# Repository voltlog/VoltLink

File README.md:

# VoltLink™
***If you would like to order one of these adapters ready assembled, check out my [Tindie store](https://www.tindie.com/products/23076/).***

VoltLink™ is a USB to serial adapter board based on the popular CP2102N chip with built-in ESP32 auto-reset circuitry. When compared to the cheap modules you can get from Aliexpress this adapter is reliable & flexible at the same time. Reliable because it's based on a well known usb to serial adapter chip sourced from a known supplier and flexible because you have the ESP32 IO & EN pin auto-reset circuit built-in so there is no need to implement this on the target board.

Another advantage of the VoltLink is the built-in 3.3V 500mA low dropout regulator capable of powering the device your are programming. Optionally you can connect a custom JST cable that alows programming of Shelly relays safely, without mains power. This makes the VoltLink one of the best usb/serial adapters to flash your devices with Tasmota or ESPHome.

You have the option of connecting through the VoltLink connector which is a JST-SH 1.0mm pitch 6 pin connector that saves space on the target board or via standard 0.1 inch pin header. 

More info about this project in [Voltlog #405](https://youtu.be/4uZt7zaJOnc).
> Please note, there have been several board revisions since I made that video.

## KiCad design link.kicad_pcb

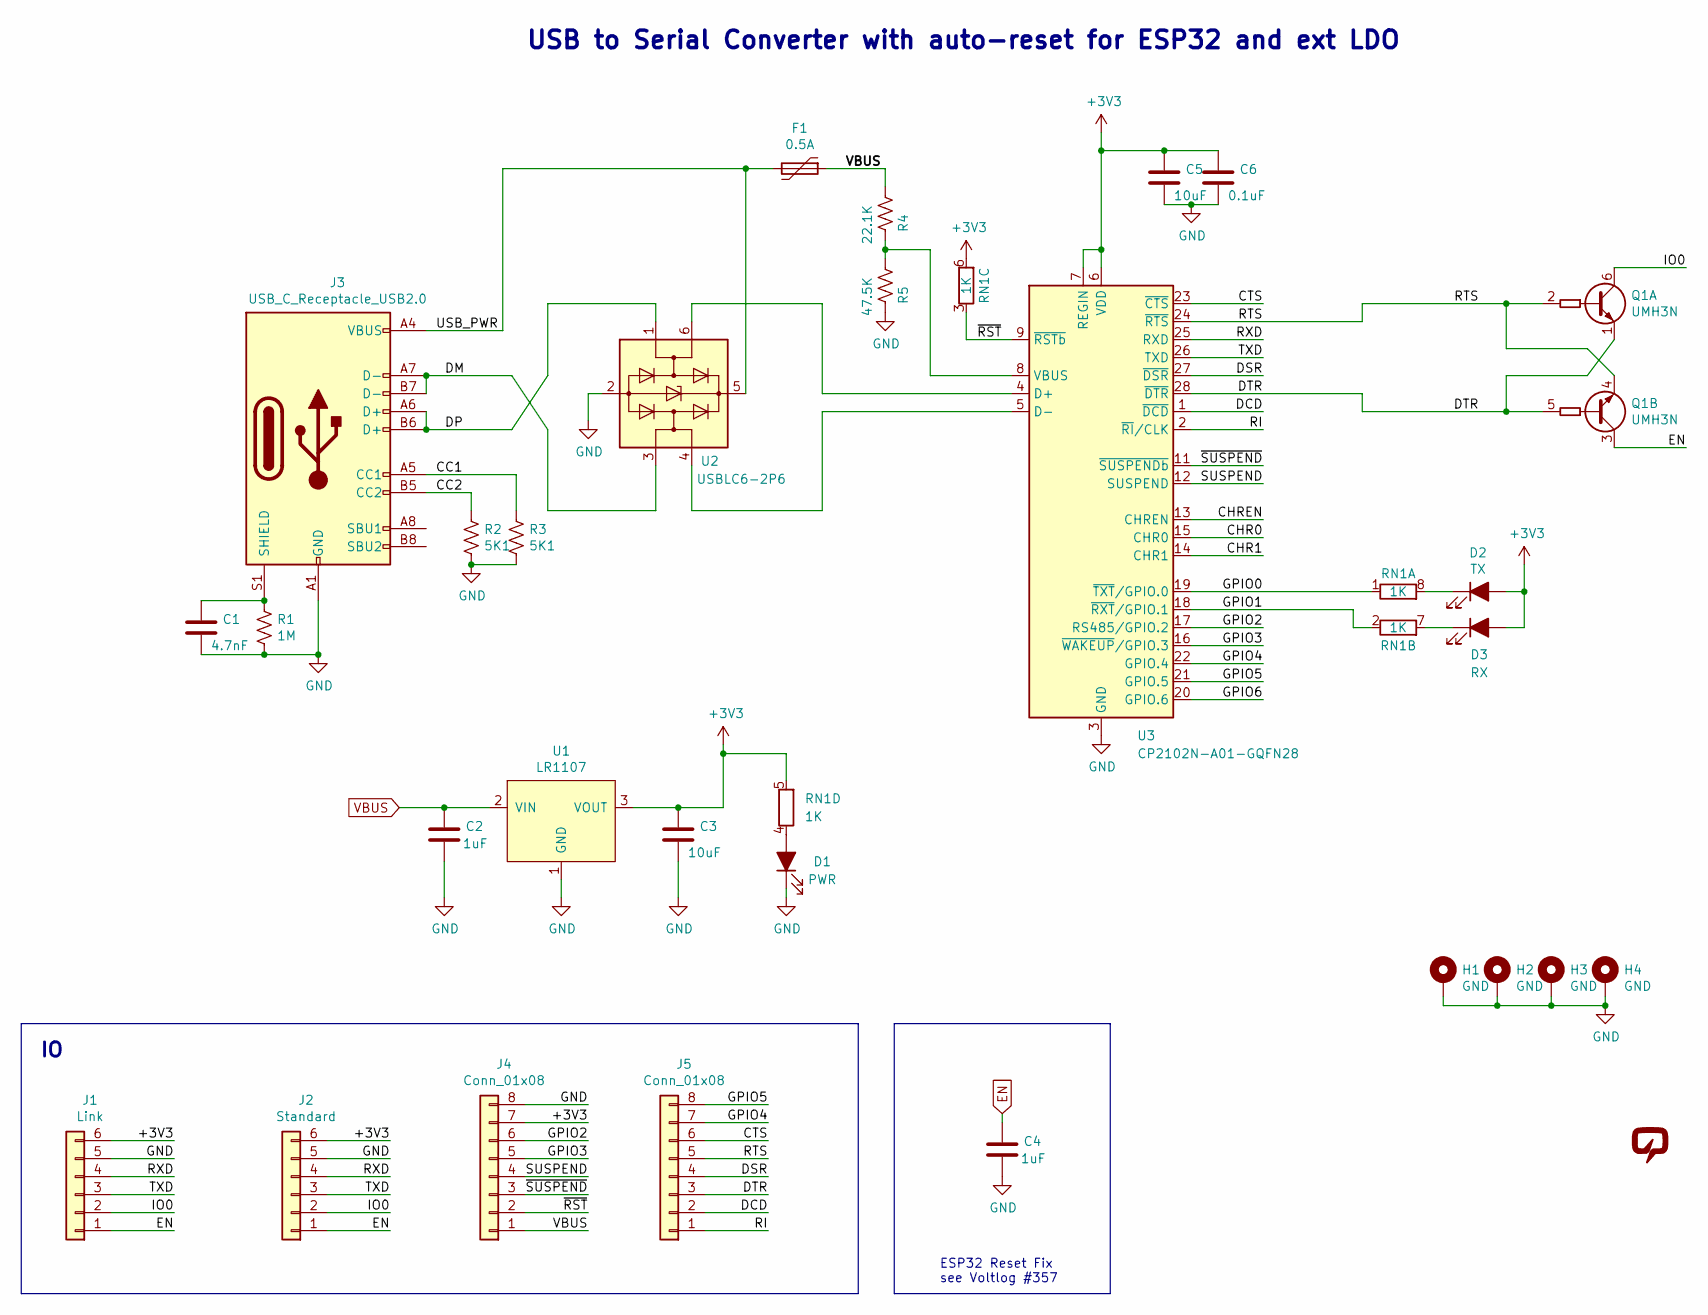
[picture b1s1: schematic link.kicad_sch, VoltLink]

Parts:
C1: 4.7nF; C_1206_3216Metric; Voltage 1KV; LCSC C107198
C2, C4: 1uF; C_0603_1608Metric; LCSC C15849
C3: 10uF; C_0603_1608Metric; Voltage 16V; LCSC C19702
C5: 10uF; C_0603_1608Metric; LCSC C19702
C6: 0.1uF; C_0603_1608Metric; LCSC C14663
D1: PWR; LED_0603_1608Metric; LCSC C193902
D2: TX; LED_0603_1608Metric; LCSC C84267
D3: RX; LED_0603_1608Metric; LCSC C193902
F1: 0.5A; Fuse_0603_1608Metric; LCSC C207014
H1, H2, H3, H4: GND; MountingHole_2.5mm_Pad
J1: Link; JST_SH_BM06B-SRSS-TB_1x06-1MP_P1.00mm_Vertical; LCSC C145963
J2: Standard; PinHeader_1x06_P2.54mm_Horizontal
J3: USB_C_Receptacle_USB2.0; TYPE-C-31-M-12; LCSC C165948
J4, J5: Conn_01x08; PinHeader_1x08_P2.54mm_Vertical
Q1: UMH3N; SOT-363_SC-70-6; LCSC C62892
R1: 1M; R_1206_3216Metric
R2, R3: 5K1; R_0603_1608Metric
R4: 22.1K; R_0603_1608Metric; LCSC C25961
R5: 47.5K; R_0603_1608Metric; LCSC C203634
RN1: 1K; R_Array_Convex_4x0603; LCSC C20197
U1: LR1107; SOT-89-3; LCSC C171498
U2: USBLC6-2P6; SOT-666; LCSC C2827693
U3: CP2102N-A01-GQFN28; QFN-28-1EP_5x5mm_P0.5mm_EP3.35x3.35mm; LCSC C1550553
V1: VOLTLOG_LOGO; voltlog_mask_3mm

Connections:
+3V3: C3.1, C5.1, C6.1, D2.2 (A), D3.2 (A), J1.6, J2.6, J4.7, RN1.5 (R4.2), RN1.6 (R3.2), U1.3 (VOUT), U3.6 (VDD), U3.7 (REGIN)
/CC1: J3.A5 (CC1), R3.1
/CC2: J3.B5 (CC2), R2.1
/CHR0: U3.15 (CHR0)
/CHR1: U3.14 (CHR1)
/CHREN: U3.13 (CHREN)
/CTS: J5.6, U3.23 (~CTS)
/DCD: J5.2, U3.1 (~DCD)
/DM: J3.A7 (D-), J3.B7 (D-), U2.3 (I/O2)
/DP: J3.A6 (D+), J3.B6 (D+), U2.1 (I/O1)
/DSR: J5.4, U3.27 (~DSR)
/DTR: J5.3, Q1.1 (E1), Q1.5 (B2), U3.28 (~DTR)
/GPIO0: RN1.1 (R1.1), U3.19 (~TXT/GPIO.0)
/GPIO1: RN1.2 (R2.1), U3.18 (~RXT/GPIO.1)
/GPIO2: J4.6, U3.17 (RS485/GPIO.2)
/GPIO3: J4.5, U3.16 (~WAKEUP/GPIO.3)
/GPIO4: J5.7, U3.22 (GPIO.4)
/GPIO5: J5.8, U3.21 (GPIO.5)
/GPIO6: U3.20 (GPIO.6)
/IO0: J1.2, J2.2, Q1.6 (C1)
/RI: J5.1, U3.2 (~RI/CLK)
/RTS: J5.5, Q1.2 (B1), Q1.4 (E2), U3.24 (~RTS)
/RXD: J1.4, J2.4, U3.25 (RXD)
/SUSPEND: J4.4, U3.12 (SUSPEND)
/TXD: J1.3, J2.3, U3.26 (TXD)
/USB_PWR: F1.2, J3.A4 (VBUS), J3.A9 (VBUS), J3.B4 (VBUS), J3.B9 (VBUS), U2.5 (VBUS)
/~RST: J4.2, RN1.3 (R3.1), U3.9 (~RSTb)
/~SUSPEND: J4.3, U3.11 (~SUSPENDb)
EN: C4.1, J1.1, J2.1, Q1.3 (C2)
GND: C1.2, C2.2, C3.2, C4.2, C5.2, C6.2, D1.1 (K), H1.1, H2.1, H3.1, H4.1, J1.5, J2.5, J3.A1 (GND), J3.A12 (GND), J3.B1 (GND), J3.B12 (GND), J4.8, R1.2, R2.2, R3.2, R5.2, U1.1 (GND), U2.2 (GND), U3.3 (GND), U3.29 (GND)
unnamed: C1.1, J3.S1 (SHIELD), R1.1
unnamed: D1.2 (A), RN1.4 (R4.1)
unnamed: D2.1 (K), RN1.8 (R1.2)
unnamed: D3.1 (K), RN1.7 (R2.2)
unnamed: R4.2, R5.1, U3.8 (VBUS)
unnamed: U2.4 (I/O2), U3.5 (D-)
unnamed: U2.6 (I/O1), U3.4 (D+)
VBUS: C2.1, F1.1, J4.1, R4.1, U1.2 (VIN)

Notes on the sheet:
ESP32 Reset Fix see Voltlog #357
USB to Serial Converter with auto-reset for ESP32 and ext LDO

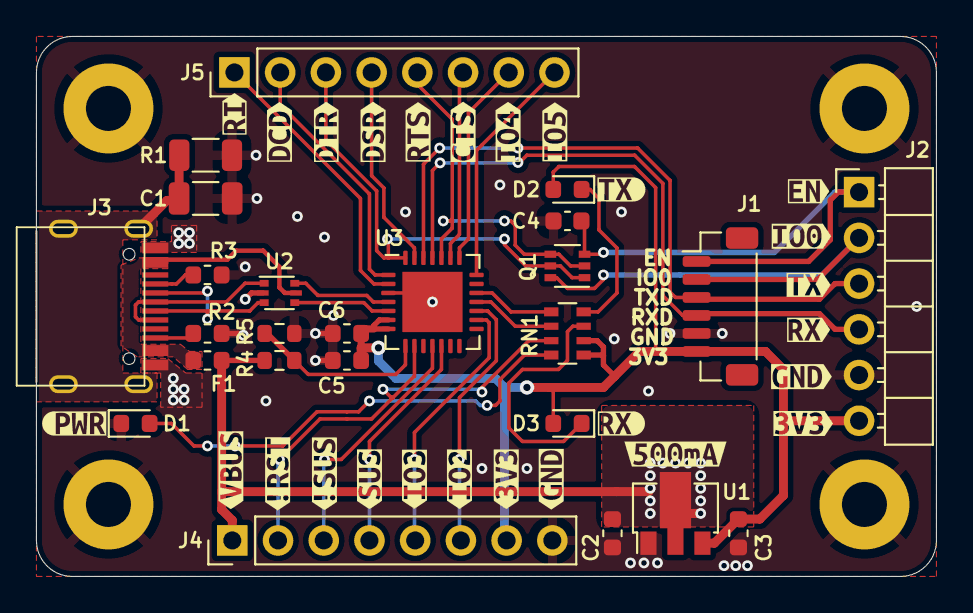
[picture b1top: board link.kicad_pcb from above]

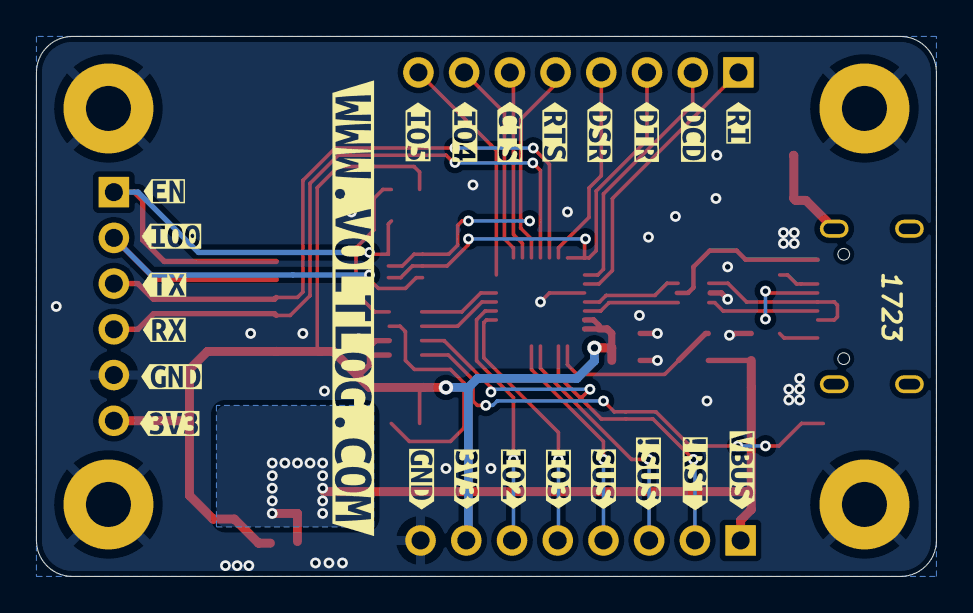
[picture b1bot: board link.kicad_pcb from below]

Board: 2 copper layers, 50.0 x 30.0 mm, 79 parts (23 on the bottom side), 34 nets.

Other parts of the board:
kibuzzard-62357A06: G***; kibuzzard-62357A06
kibuzzard-62357A8A: G***; kibuzzard-62357A8A
kibuzzard-62357A41: G***; kibuzzard-62357A41
kibuzzard-62357AC8: G***; kibuzzard-62357AC8
kibuzzard-62357AF5: G***; kibuzzard-62357AF5
kibuzzard-62357B6B: G***; kibuzzard-62357B6B
kibuzzard-62357B8F: G***; kibuzzard-62357B8F
kibuzzard-62357B09: G***; kibuzzard-62357B09
kibuzzard-62357B9D: G***; kibuzzard-62357B9D
kibuzzard-62357B18: G***; kibuzzard-62357B18
kibuzzard-62357B23: G***; kibuzzard-62357B23
kibuzzard-62357B61: G***; kibuzzard-62357B61
kibuzzard-62357B85: G***; kibuzzard-62357B85
kibuzzard-62357B96: G***; kibuzzard-62357B96
kibuzzard-62357BA3: G***; kibuzzard-62357BA3
kibuzzard-62357BA9: G***; kibuzzard-62357BA9
kibuzzard-62357BE4: G***; kibuzzard-62357BE4
kibuzzard-62357BED: G***; kibuzzard-62357BED
kibuzzard-62357BF2: G***; kibuzzard-62357BF2
kibuzzard-62357BF8: G***; kibuzzard-62357BF8
kibuzzard-62357BFE: G***; kibuzzard-62357BFE
kibuzzard-62357C0A: G***; kibuzzard-62357C0A
kibuzzard-62357C11: G***; kibuzzard-62357C11
kibuzzard-62357C18: G***; kibuzzard-62357C18
kibuzzard-623575FB: G***; kibuzzard-623575FB
kibuzzard-623576E7: G***; kibuzzard-623576E7
kibuzzard-623576F6: G***; kibuzzard-623576F6
kibuzzard-623577BD: G***; kibuzzard-623577BD
kibuzzard-623577CF: G***; kibuzzard-623577CF
kibuzzard-623577DC: G***; kibuzzard-623577DC
kibuzzard-623577E9: G***; kibuzzard-623577E9
kibuzzard-623577F4: G***; kibuzzard-623577F4
kibuzzard-623578AD: G***; kibuzzard-623578AD
kibuzzard-623578BA: G***; kibuzzard-623578BA
kibuzzard-623579BD: G***; kibuzzard-623579BD
kibuzzard-623579CB: G***; kibuzzard-623579CB
kibuzzard-623579D6: G***; kibuzzard-623579D6
kibuzzard-623579E1: G***; kibuzzard-623579E1
kibuzzard-623579ED: G***; kibuzzard-623579ED
kibuzzard-623579F4: G***; kibuzzard-623579F4
kibuzzard-623579FF: G***; kibuzzard-623579FF
kibuzzard-6235760A: G***; kibuzzard-6235760A
kibuzzard-62357631: G***; kibuzzard-62357631
kibuzzard-62357705: G***; kibuzzard-62357705
kibuzzard-62357716: G***; kibuzzard-62357716
kibuzzard-62357727: G***; kibuzzard-62357727
kibuzzard-62357731: G***; kibuzzard-62357731
kibuzzard-62357776: G***; kibuzzard-62357776
kibuzzard-62357894: G***; kibuzzard-62357894

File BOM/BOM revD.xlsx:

VoltLink revD Bill Of Materials
Qty | Reference(s) | Value | Footprint | Datasheet | LCSC | PN | Voltage | Tolerance
1 | C1 | 4.7nF | Capacitor_SMD:C_1206_3216Metric | ~ | C107198 | CC1206KKX7RCBB472 | 1KV | ±10%
2 | C2, C4 | 1uF | Capacitor_SMD:C_0603_1608Metric | ~ | C1592 | CL10A105KO8NNNC | 16V | ±10%
2 | C3, C5 | 10uF | Capacitor_SMD:C_0603_1608Metric | ~ | C92487 | CL10A106MO8NQNC | 16V | ±20%
1 | C6 | 0.1uF | Capacitor_SMD:C_0603_1608Metric | ~ | C24452 | CL10B104JB8NNNC | 50V | ±5%
1 | D1 | SP0503BAHT | Package_TO_SOT_SMD:SOT-143 | http://www.littelfuse.com/~/media/files/littelfuse/technical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 | C2682275 | TPSP0503BAHTG | - | -
1 | D2, D4 | PWR, RX GREEN | LED_SMD:LED_0603_1608Metric | https://datasheet.lcsc.com/lcsc/2008201033_Foshan-NationStar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 | C193902 | NCD0603R5 | - | -
1 | D3 | TX RED | LED_SMD:LED_0603_1608Metric | https://datasheet.lcsc.com/lcsc/2008201032_Foshan-NationStar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 | C84267 | NCD0603G1 | - | -
1 | F1 | 0.5A | Fuse:Fuse_0603_1608Metric | ~ | C207014 | 0603L050SLYR | - | -
1 | J1 | Link | Connector_JST:JST_SH_BM06B-SRSS-TB_1x06-1MP_P1.00mm_Vertical | ~ | C145963 | BOOMELE VERTICAL | - | -
1 | J2 | Standard | Connector_PinHeader_2.54mm:PinHeader_1x06_P2.54mm_Horizontal | ~ | DNP | DNP | DNP | DNP
1 | J3 | USB_C_Receptacle_USB2.0 | voltlog:TYPE-C-31-M-12 | https://www.usb.org/sites/default/files/documents/usb_type-c.zip | C165948 | TYPE-C-31-M-12 | - | -
2 | J4, J5 | Conn_01x08 | Connector_PinHeader_2.54mm:PinHeader_1x08_P2.54mm_Vertical | ~ | DNP | DNP | DNP | DNP
1 | Q1 | UMH3N | Package_TO_SOT_SMD:SOT-363_SC-70-6 | http://rohmfs.rohm.com/en/products/databook/datasheet/discre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 | C62892 | UMH3N | - | -
1 | R1 | 1M | Resistor_SMD:R_1206_3216Metric | ~ |  | generic |  | 0.01
2 | R2, R3 | 5K1 | Resistor_SMD:R_0603_1608Metric | ~ |  | generic |  | 0.01
1 | R4 | 22.1K | Resistor_SMD:R_0603_1608Metric | ~ |  | generic |  | 0.01
1 | R5 | 47.5K | Resistor_SMD:R_0603_1608Metric | ~ |  | generic |  | 0.01
1 | RN1 | 1K | Resistor_SMD:R_Array_Convex_4x0603 | ~ | C425239 | 4D03WGF1001T5E |  | 0.01
1 | U1 | LR1107 | Package_TO_SOT_SMD:SOT-89-3 | https://datasheet.lcsc.com/lcsc/1809251634_UTC-Unisonic-Tech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 | C171498 | LR1107G-33-AB3-C-R | - | -
1 | U2 | CP2102N-A01-GQFN28 | Package_DFN_QFN:QFN-28-1EP_5x5mm_P0.5mm_EP3.35x3.35mm | https://www.silabs.com/documents/public/data-sheets/cp2102n-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 | C964632 | CP2102N-A02-GQFN28R | - | -

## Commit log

2021-03-15 Initial commit of files
2021-03-15 Added board image
2021-10-05 Added image of the board
2022-02-14 Release revC
2022-02-14 added gitignore
2022-02-14 removed kicad backups
2022-02-14 Added README
2022-02-14 Added PCB image
2022-04-24 release revD
2022-04-30 Release revE
2022-04-30 removed old files
2024-02-28 revE release

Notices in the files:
link.kicad_sch:
GPL-3.0 License
